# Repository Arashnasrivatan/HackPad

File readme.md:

# Macropad V1

This is a small macropad with 6 mechanical switches and a rotary encoder  
Its made to make common actions easier like copy, paste, cut, switching windows and ...

## Purpose

I built this for Hack Club  
I wanted to learn how to make the macropad from the beginning  
PCB design --> KiCad  
3D modeling --> Fusion 360  
Firmware --> Python KMK

My focus was on learning

## Photos

### Final View

.png?raw=true)

### Schematic

.png?raw=true)

### PCB

.png?raw=true)

### Case Assembly

.png?raw=true)

## Parts List | BOM

| Item | Designator | Footprint | Quantity | Part |
|------|------------|-----------|----------|------|
| 1 | U1 | XIAO-RP2040-DIP | 1 | XIAO-RP2040-DIP |
| 2 | SW7 | RotaryEncoder_Alps_EC11E-Switch_Vertical_H20mm | 1 | RotaryEncoder_Switch |
| 3 | SW1, SW2, SW3, SW4, SW5, SW6 | SW_Cherry_MX_1.00u_PCB | 6 | SW_Push |
| 4 | D1, D2 | LED_SK6812MINI_PLCC4_3.5x3.5mm_P1.75mm | 2 | SK6812MINI |

## csv file  
[macropad.csv](macropad.csv)

## Cart screenshot

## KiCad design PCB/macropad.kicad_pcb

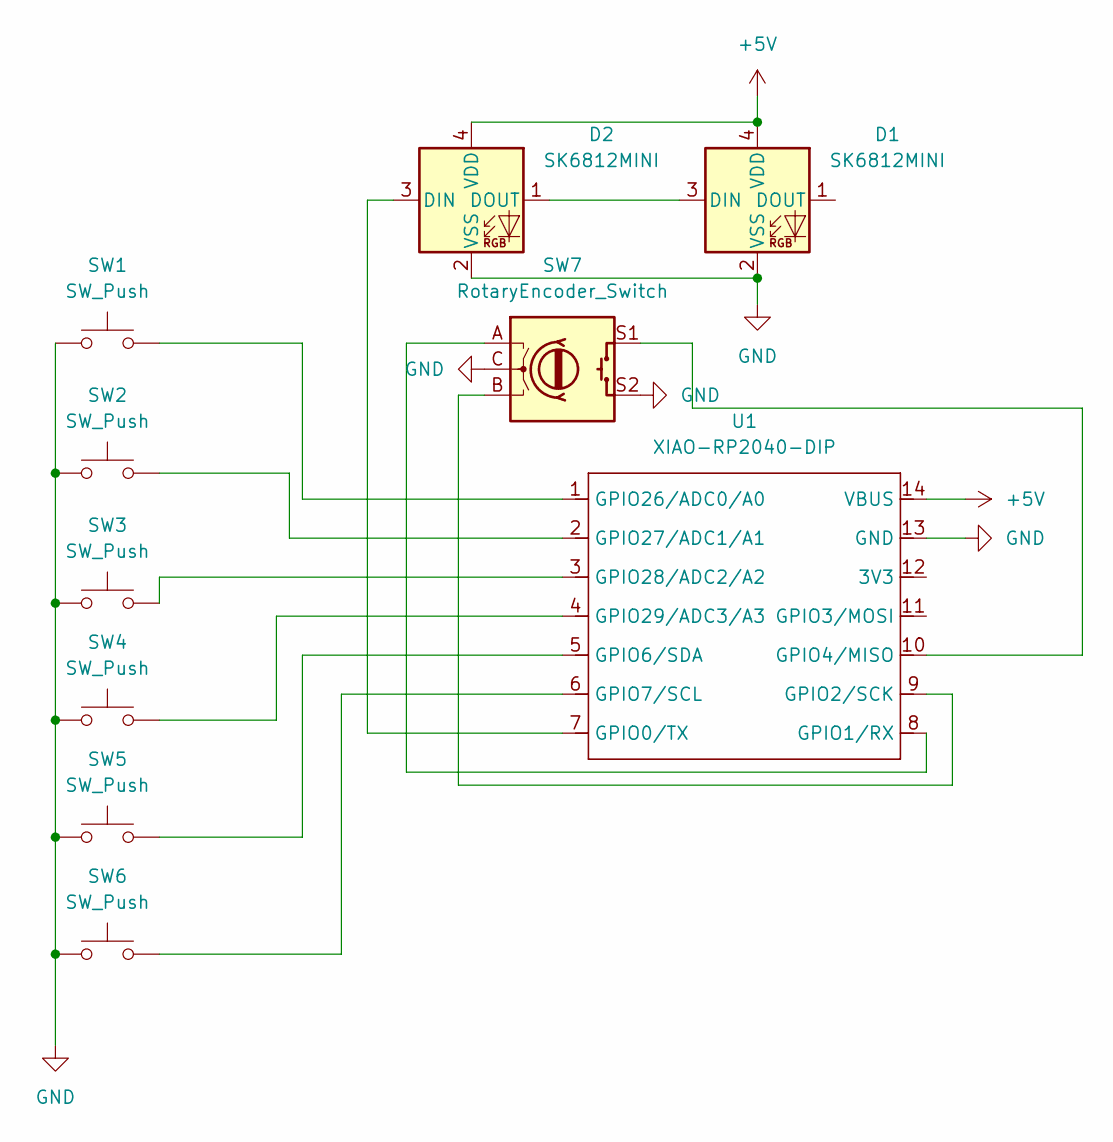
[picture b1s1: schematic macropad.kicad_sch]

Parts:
D1, D2: SK6812MINI; LED_SK6812MINI_PLCC4_3.5x3.5mm_P1.75mm
SW1, SW2, SW3, SW4, SW5, SW6: SW_Push; SW_Cherry_MX_1.00u_PCB
SW7: RotaryEncoder_Switch; RotaryEncoder_Alps_EC11E-Switch_Vertical_H20mm
U1: XIAO-RP2040-DIP

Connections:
+5V: D1.4 (VDD), D2.4 (VDD), U1.14 (VBUS)
GND: D1.2 (VSS), D2.2 (VSS), SW1.1, SW2.1, SW3.1, SW4.1, SW5.1, SW6.1, SW7.C, SW7.S2, U1.13 (GND)
unnamed: D1.3 (DIN), D2.1 (DOUT)
unnamed: D2.3 (DIN), U1.7 (GPIO0/TX)
unnamed: SW7.A, U1.8 (GPIO1/RX)
unnamed: SW7.B, U1.9 (GPIO2/SCK)
unnamed: SW7.S1, U1.10 (GPIO4/MISO)
unnamed: SW5.2, U1.5 (GPIO6/SDA)
unnamed: SW6.2, U1.6 (GPIO7/SCL)
unnamed: SW1.2, U1.1 (GPIO26/ADC0/A0)
unnamed: SW2.2, U1.2 (GPIO27/ADC1/A1)
unnamed: SW3.2, U1.3 (GPIO28/ADC2/A2)
unnamed: SW4.2, U1.4 (GPIO29/ADC3/A3)

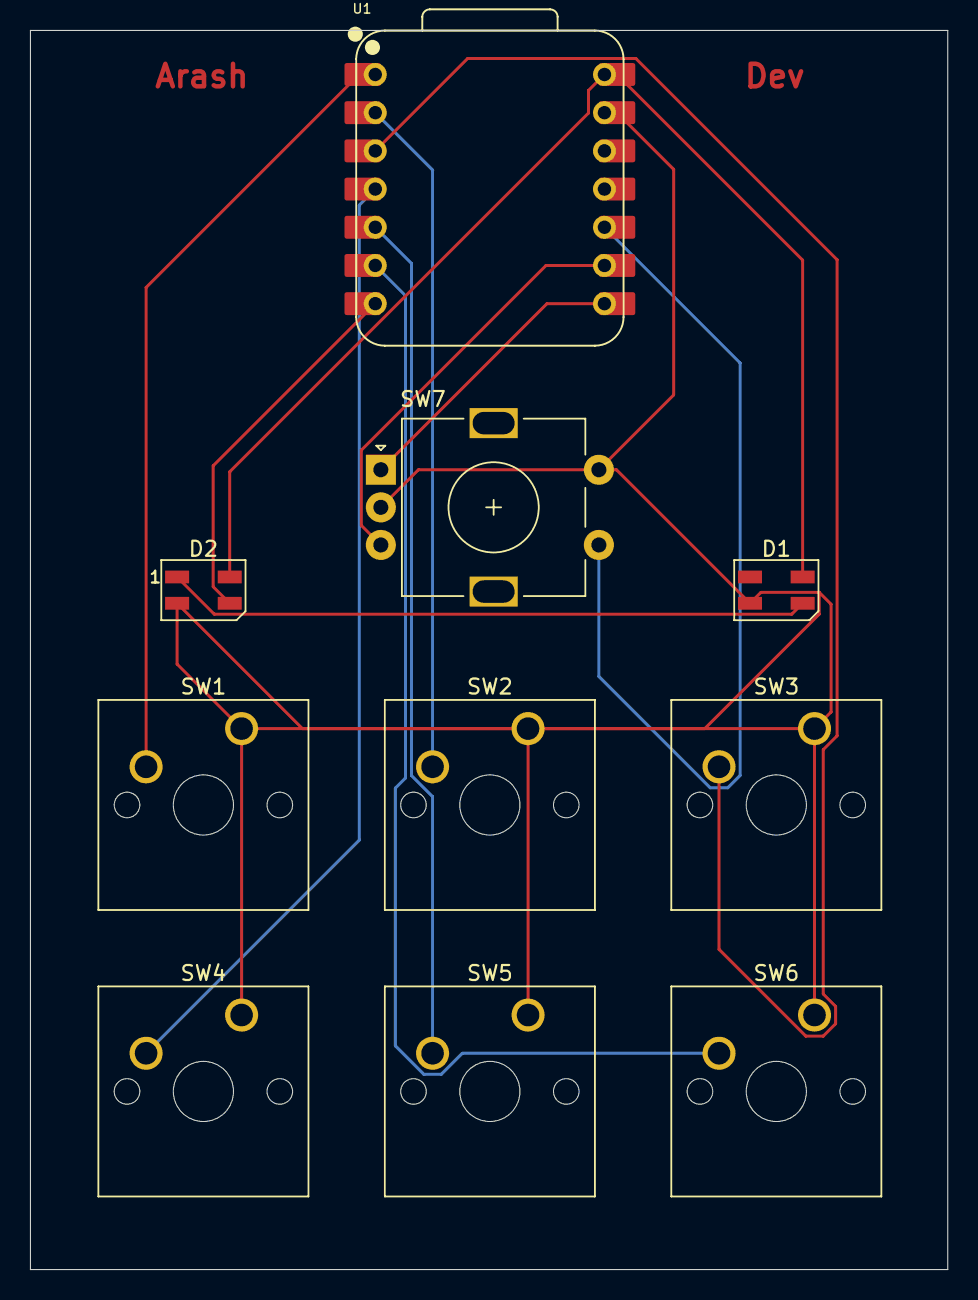
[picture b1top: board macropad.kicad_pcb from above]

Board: 2 copper layers, 61.0 x 82.4 mm, 10 parts (0 on the bottom side), 13 nets.

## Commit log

2025-12-12 hackpad V2
2025-12-12 force replace content
2025-12-12 fix: fix some readme bugs and add cart.png
2025-12-12 fix: rename 'hackpad (2).png' to 'hackpad (2).png'
